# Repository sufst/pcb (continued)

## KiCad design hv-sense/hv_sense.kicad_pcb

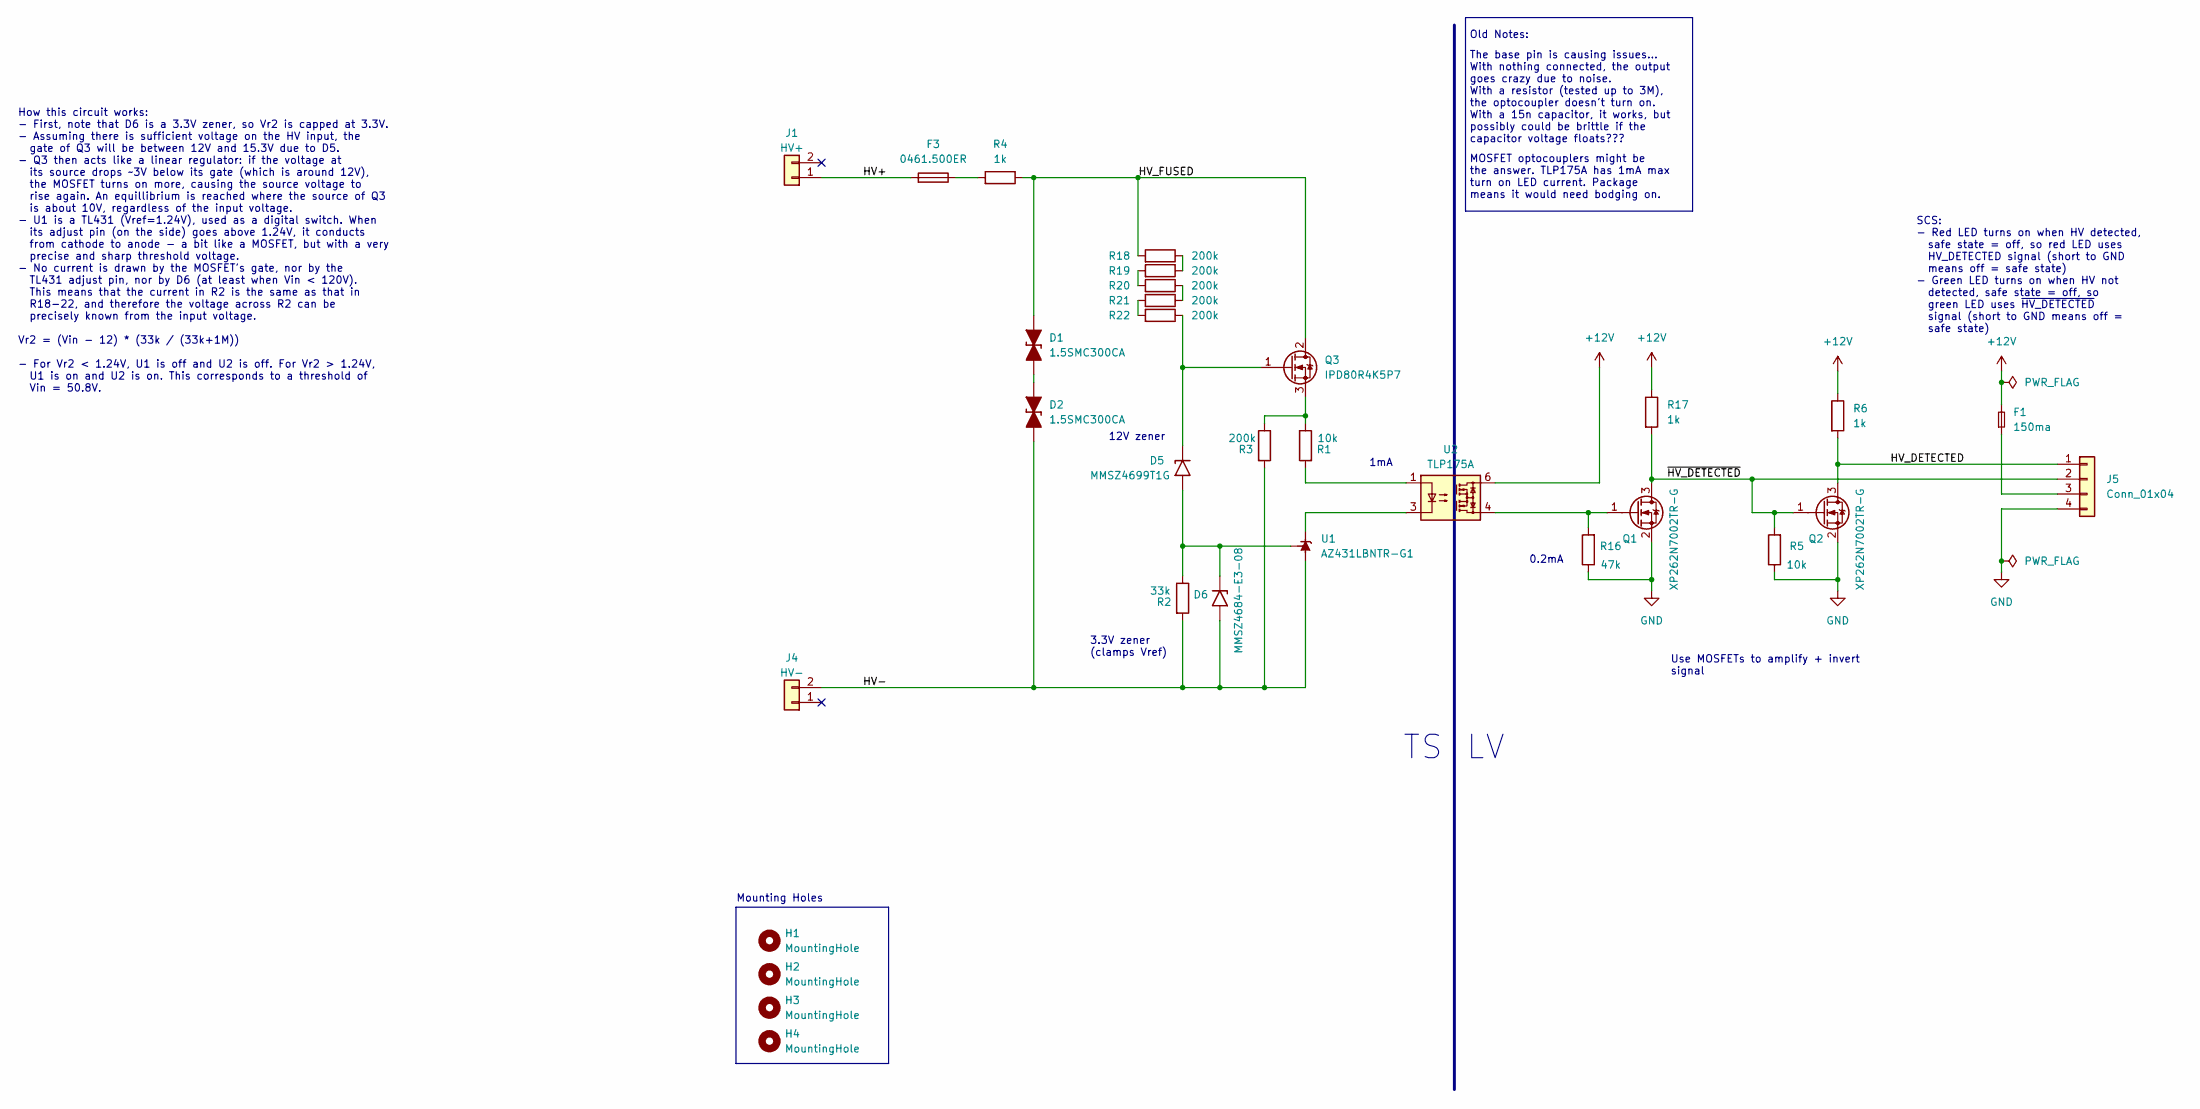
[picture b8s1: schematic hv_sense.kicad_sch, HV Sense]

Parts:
D1, D2: 1.5SMC300CA; D_SMC_TVS
D5: MMSZ4699T1G; D_SOD-123
D6: MMSZ4684-E3-08; D_SOD-123
F1: 150ma; Fuse_0805_2012Metric
F3: 0461.500ER; Littelfuse-04611-25ER
H1, H2, H3, H4: MountingHole; MountingHole_4.3mm_M4
J1: HV+; Molex_Micro-Fit_3.0_43045-0212_2x01_P3.00mm_Vertical
J4: HV-; Molex_Micro-Fit_3.0_43045-0212_2x01_P3.00mm_Vertical
J5: Conn_01x04; Molex_Micro-Fit_3.0_43045-0412_2x02_P3.00mm_Vertical
Q1, Q2: XP262N7002TR-G; SOT-23
Q3: IPD80R4K5P7; TO-252-2
R1, R5: 10k; R_0805_2012Metric_Pad1.20x1.40mm_HandSolder
R2: 33k; R_0805_2012Metric_Pad1.20x1.40mm_HandSolder
R3, R18, R19, R20, R21, R22: 200k; R_0805_2012Metric_Pad1.20x1.40mm_HandSolder
R4: 1k; R_2512_6332Metric
R6, R17: 1k; R_0805_2012Metric_Pad1.20x1.40mm_HandSolder
R16: 47k; R_0805_2012Metric_Pad1.20x1.40mm_HandSolder
U1: AZ431LBNTR-G1; SOT-23_Handsoldering
U2: TLP175A; MFSOP6-4_4.4x3.6mm_P1.27mm

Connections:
+12V: F1.2, R6.1, R17.1, U2.6
/HV+: F3.2, J1.1
/HV-: D2.1 (K), D6.2 (A2), J4.2, R2.2, R3.2, U1.3 (A)
/HV_DETECTED: J5.1, Q2.3 (D), R6.2
/HV_FUSED: D1.2 (A), Q3.2 (D), R4.1, R18.2
/~HV_DETECTED: J5.2, Q1.3 (D), Q2.1 (G), R5.2, R17.2
GND: J5.4, Q1.2 (S), Q2.2 (S), R5.1, R16.1
unnamed: D1.1 (K), D2.2 (A)
unnamed: D5.1 (A1), Q3.1 (G), R22.1
unnamed: D5.2 (A2), D6.1 (A1), R2.1, U1.1 (REF)
unnamed: F3.1, R4.2
unnamed: F1.1, J5.3
unnamed: Q1.1 (G), R16.2, U2.4
unnamed: Q3.3 (S), R1.1, R3.1
unnamed: R1.2, U2.1
unnamed: R18.1, R19.1
unnamed: R19.2, R20.2
unnamed: R20.1, R21.1
unnamed: R21.2, R22.2
unnamed: U1.2 (K), U2.3

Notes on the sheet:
0.2mA
SCS: - Red LED turns on when HV detected, safe state = off, so red LED uses HV_DETECTED signal (short to GND means off = safe state) - Green LED turns on when HV not detected, safe state = off, so green LED uses ~{HV_DETECTED} signal (short to GND means off = safe state)
Mounting Holes
12V zener
Use MOSFETs to amplify + invert signal
How this circuit works: - First, note that D6 is a 3.3V zener, so Vr2 is capped at 3.3V. - Assuming there is sufficient voltage on the HV input, the gate of Q3 will be between 12V and 15.3V due to D5. - Q3 then acts like a linear regulator: if the voltage at its source drops ~3V below its gate (whi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
3.3V zener (clamps Vref)
Old Notes:
The base pin is causing issues... With nothing connected, the output goes crazy due to noise. With a resistor (tested up to 3M), the optocoupler doesn't turn on. With a 15n capacitor, it works, but possibly could be brittle if the capacitor voltage floats???
1mA
MOSFET optocouplers might be the answer. TLP175A has 1mA max turn on LED current. Package means it would need bodging on.

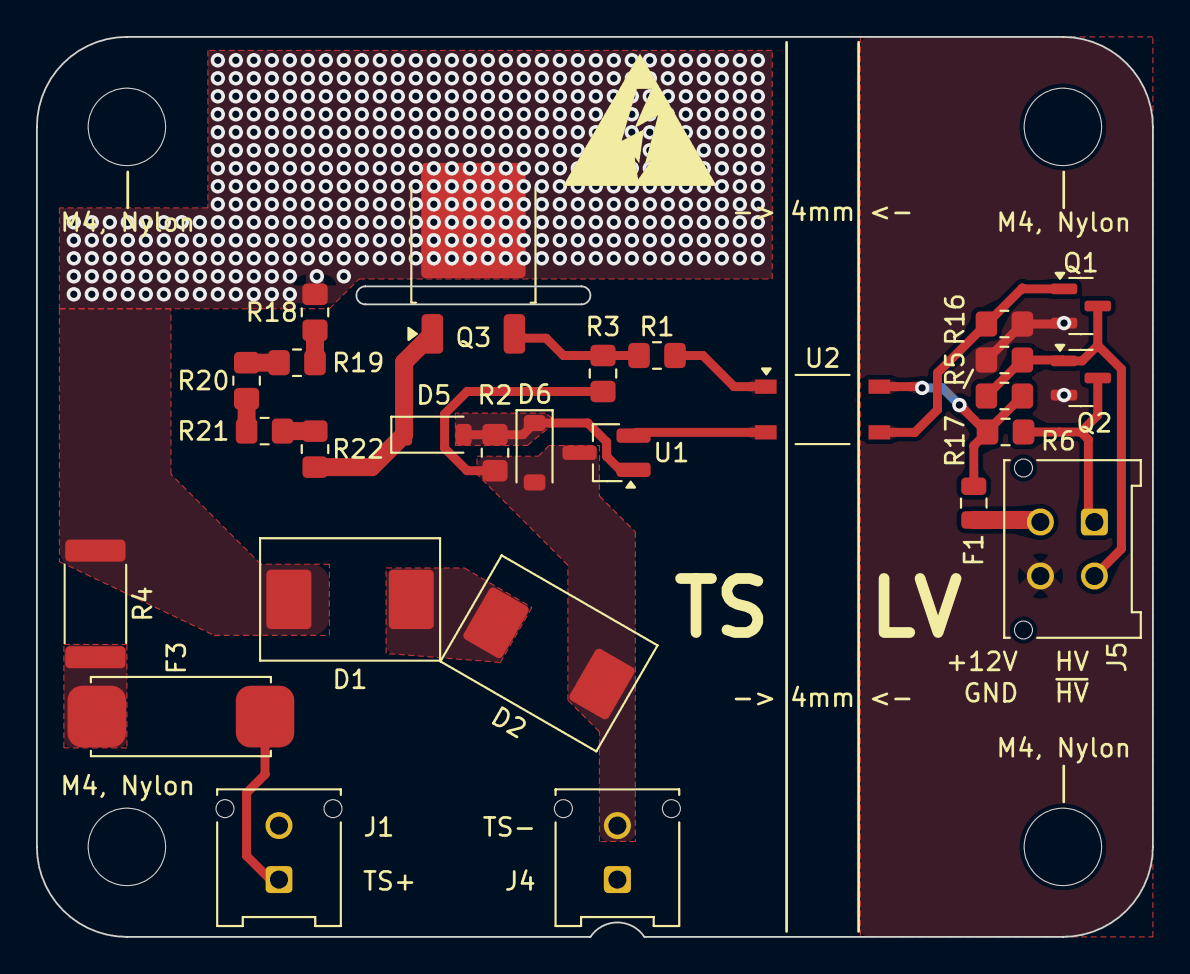
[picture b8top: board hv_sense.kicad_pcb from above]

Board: 2 copper layers, 62.0 x 50.0 mm, 31 parts (0 on the bottom side), 20 nets.

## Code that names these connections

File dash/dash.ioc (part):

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Mcu.Name=STM32F746ZGTx
Mcu.Package=LQFP144
Mcu.UserName=STM32F746ZGTx
PA0/WKUP.GPIOParameters=GPIO_Label
PA0/WKUP.GPIO_Label=BACKLIGHT_PWM
PA0/WKUP.Signal=S_TIM2_CH1_ETR
PA1.Mode=RGB666
PA1.Signal=LTDC_R2
PA11.Mode=CAN_Activate
PA11.Signal=CAN1_RX
PA12.Mode=CAN_Activate
PA12.Signal=CAN1_TX
PA15.GPIOParameters=GPIO_Label
PA15.GPIO_Label=SD_CARD_DETECT
PA15.Signal=GPIO_Output
PA3.Mode=RGB666
PA3.Signal=LTDC_B5
PA4.Mode=RGB666
PA4.Signal=LTDC_VSYNC
PA5.Mode=RGB666
PA5.Signal=LTDC_R4
PA6.Mode=RGB666
PA6.Signal=LTDC_G2
PA7.Signal=FMC_SDNWE
PB0.Mode=RGB666
PB0.Signal=LTDC_R3
PB1.Mode=RGB666
PB1.Signal=LTDC_R6
PB10.Mode=RGB666
PB10.Signal=LTDC_G4
PB11.Mode=RGB666
PB11.Signal=LTDC_G5
PB12.GPIOParameters=GPIO_Label
PB12.GPIO_Label=SPI2_CS
PB12.Signal=GPIO_Output
PB13.Mode=Full_Duplex_Master
PB13.Signal=SPI2_SCK
PB14.Mode=Full_Duplex_Master
PB14.Signal=SPI2_MISO
PB15.Mode=Full_Duplex_Master
PB15.Signal=SPI2_MOSI
PB5.Mode=CAN_Activate
PB5.Signal=CAN2_RX
PB6.Mode=CAN_Activate
PB6.Signal=CAN2_TX
PB8.Mode=RGB666
PB8.Signal=LTDC_B6
PB9.Mode=RGB666
PB9.Signal=LTDC_B7
PC0.Mode=RGB666
PC0.Signal=LTDC_R5
PC10.Mode=SD_4_bits_Wide_bus
PC10.Signal=SDMMC1_D2
PC11.Mode=SD_4_bits_Wide_bus
PC11.Signal=SDMMC1_D3
PC12.Mode=SD_4_bits_Wide_bus
PC12.Signal=SDMMC1_CK
PC2.Mode=SdramChipSelect1_1
PC2.Signal=FMC_SDNE0
PC3.Mode=SdramChipSelect1_1
PC3.Signal=FMC_SDCKE0
PC5.GPIOParameters=GPIO_Label
PC5.GPIO_Label=LCD_DISP
PC5.Signal=GPIO_Output
PC6.Mode=RGB666
PC6.Signal=LTDC_HSYNC
PC7.Mode=RGB666
PC7.Signal=LTDC_G6
PC8.Mode=SD_4_bits_Wide_bus
PC8.Signal=SDMMC1_D0
PC9.Mode=SD_4_bits_Wide_bus
PC9.Signal=SDMMC1_D1
PD0.Signal=FMC_D2_DA2
PD1.Signal=FMC_D3_DA3
PD10.Signal=FMC_D15_DA15
PD11.GPIOParameters=GPIO_Label
PD11.GPIO_Label=TOUCH_IRQ
PD11.Signal=GPXTI11
PD12.GPIOParameters=GPIO_Label
PD12.GPIO_Label=TOUCH_BUSY
PD12.Signal=GPIO_Input
PD14.Signal=FMC_D0_DA0
PD15.Signal=FMC_D1_DA1
PD2.Mode=SD_4_bits_Wide_bus
PD2.Signal=SDMMC1_CMD
PD3.Mode=RGB666
PD3.Signal=LTDC_G7
PD6.Mode=RGB666
PD6.Signal=LTDC_B2
PD8.Signal=FMC_D13_DA13
PD9.Signal=FMC_D14_DA14
PE0.Signal=FMC_NBL0
PE1.Signal=FMC_NBL1
PE10.Signal=FMC_D7_DA7
PE11.Signal=FMC_D8_DA8
PE12.Signal=FMC_D9_DA9
PE13.Signal=FMC_D10_DA10
PE14.Signal=FMC_D11_DA11
PE15.Signal=FMC_D12_DA12
PE7.Signal=FMC_D4_DA4
PE8.Signal=FMC_D5_DA5
PE9.Signal=FMC_D6_DA6
PF0.Signal=FMC_A0
PF1.Signal=FMC_A1
PF10.Mode=RGB666
PF10.Signal=LTDC_DE
PF11.Signal=FMC_SDNRAS
PF12.Signal=FMC_A6
PF13.Signal=FMC_A7
PF14.Signal=FMC_A8
PF15.Signal=FMC_A9
PF2.Signal=FMC_A2
PF3.Signal=FMC_A3
PF4.Signal=FMC_A4
PF5.Signal=FMC_A5
PG0.Signal=FMC_A10
PG1.Signal=FMC_A11
PG10.Mode=RGB666
PG10.Signal=LTDC_G3
PG11.Mode=RGB666
PG11.Signal=LTDC_B3
PG12.Mode=RGB666
PG12.Signal=LTDC_B4
PG15.Signal=FMC_SDNCAS
PG4.Signal=FMC_A14_BA0
PG5.Signal=FMC_A15_BA1
PG6.Mode=RGB666
PG6.Signal=LTDC_R7
PG7.Mode=RGB666
PG7.Signal=LTDC_CLK
PG8.Signal=FMC_SDCLK
RCC.HSE_VALUE=25000000
board=custom

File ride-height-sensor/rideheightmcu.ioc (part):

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Mcu.Name=STM32C092FBPx
Mcu.Package=TSSOP20
Mcu.UserName=STM32C092FBPx
PA0.GPIOParameters=GPIO_Label
PA0.GPIO_Label=PPS_IN
PA0.Signal=S_TIM1_CH1
PA1.GPIOParameters=GPIO_Label
PA1.GPIO_Label=JPR1
PA1.Signal=GPIO_Input
PA11\ [PA9].Mode=FDCAN_Activate
PA11\ [PA9].Signal=FDCAN1_RX
PA12\ [PA10].Mode=FDCAN_Activate
PA12\ [PA10].Signal=FDCAN1_TX
PA13.Mode=Serial_Wire
PA13.Signal=DEBUG_SWDIO
PA14-BOOT0.Mode=Serial_Wire
PA14-BOOT0.Signal=DEBUG_SWCLK
PA14-BOOT0__PA15.StandardMode=true
PA2.GPIOParameters=GPIO_Label
PA2.GPIO_Label=JPR2
PA2.Signal=GPIO_Input
PA3.GPIOParameters=GPIO_Label
PA3.GPIO_Label=XSHUT
PA3.Signal=GPIO_Output
PA4.GPIOParameters=GPIO_Label
PA4.GPIO_Label=BTN
PA4.Signal=GPIO_Input
PA5.GPIOParameters=GPIO_Label
PA5.GPIO_Label=LED_ACTIVITY
PA5.Signal=GPIO_Output
PA6.GPIOParameters=GPIO_Label
PA6.GPIO_Label=LED_CAN_ACTIVITY
PA6.Signal=GPIO_Output
PA7.GPIOParameters=GPIO_Label
PA7.GPIO_Label=LED_HEARTBEAT
PA7.Signal=GPIO_Output
PB0.GPIOParameters=GPIO_Label
PB0.GPIO_Label=interrupt pin
PB0.Signal=GPXTI0
PB0__PB1__PB2__PA8.StandardMode=true
PB3__PB4__PB5__PB6.StandardMode=true
PB6.Mode=I2C
PB6.Signal=I2C1_SCL
PB7.Mode=I2C
PB7.Signal=I2C1_SDA
PB7__PB8.StandardMode=true
PC14-OSCX_IN(PC14).Mode=HSE-External-Oscillator
PC14-OSCX_IN(PC14).Signal=RCC_OSCX_IN
PC15-OSCX_OUT(PC15).Mode=HSE-External-Oscillator
PC15-OSCX_OUT(PC15).Signal=RCC_OSCX_OUT
RCC.HSE_VALUE=25000000
RCC.SYSCLKFreq_VALUE=25000000
RCC.SYSCLKSource=RCC_SYSCLKSOURCE_HSE
board=custom

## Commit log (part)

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2026-02-04 Reviewing with anna
2026-02-05 Added buck-boost schematic
2026-02-05 Via farms are a lie made by big drill to sell more drill bits
2026-02-05 Adding 3d models, changing resistors
2026-02-05 Reviewing and changing
2026-02-05 Add warning
2026-02-06 Added flat clamp instead of unidirectional tvs
2026-02-07 Updated BOM, ready for review
2026-02-07 move silkscreen
2026-02-07 Generated pdf
2026-02-07 Partially complete BOM
    under Mouser project "New VCU"
2026-02-07 Add clamped_div schematic and update symbols/libs
    Add a new clamped_div.kicad_sch implementing a voltage divider/clamped input (optional zener diodes, resistor network and notes). Update therm.kicad_sch to include a project title block and add an ES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
2026-02-07 BOM Complete
2026-02-09 Updated BOM
2026-02-10 archive sensor board
2026-02-10 rename thermistor board to can-node
2026-02-10 finish can-node schematic, some libraries are missing
2026-02-10 Done mostly all of design for schematic
    Hello everybody my name is markiplier,
    need to add connectors to schematic
    **IGNORE GPS PCB IT IS OUTDATED**
2026-02-10 Schematic done i think
    Peetah The Horse Is Here
2026-02-10 switch B.Cu and In1.Cu routing, update silkscreen and other fixes
2026-02-12 Added 26 pin harwin connector
2026-02-12 Update TLV9101IDBVR
2026-02-12 Added buffered input
    Also footprint assignments messed up rip
2026-02-12 forgot to save
2026-02-13 Implemented APPS SCS biasing
    TODO: fusing buck-boost regulated output?
2026-02-17 Made the file
2026-02-17 help
2026-02-17 traces to 0.5 and footprint to 0805 done
2026-02-17 pcbdesign
2026-02-17 made it a lill bit neater
    not much
2026-02-17 added the logo and version
    still need to add the pin, button descriptions and basic labels
2026-02-17 gOTrIDoFtHEcAMELS
2026-02-17 Added outline of pcb
2026-02-18 reroute can-node
2026-02-18 fix some silkscreen issues + add more vias
2026-02-18 try and fix issue with git
2026-02-19 SILKSCREEN DONNEEE!!!
2026-02-19 routing fixes
2026-02-20 Changes
    Production on pause
2026-02-21 production files
2026-02-21 Update to only have CAN, move BMS taps to loom
2026-02-24 Added necessary STM things to schematic
2026-02-24 Footprint for mating card made
2026-02-24 Added camera and layout things
2026-02-25 Oopsie relocated mating card footprint to vcu-debug-card from vcu
2026-02-25 Pinned SUFST library why is github being weird :(
2026-02-25 Added some leds :)
2026-02-26 Attempted to fix merge error
2026-03-01 Switched back to molex
2026-03-01 saved schematic
2026-03-02 Added Apps sensor
2026-03-03 Added mating card footprint to symbol
2026-03-03 addeed I2C sevensegs
2026-03-03 Added footprint for seven segment display
2026-03-03 Changed name of seven segment and added link to datasheet
2026-03-03 Footprint :(
2026-03-03 added dip BOOYAH
2026-03-05 uhhh
2026-03-08 connected dip
2026-03-09 Updated mating card footprint
    Added the gap for pins 15 and 16 and the part at the bottom
2026-03-10 added values
2026-03-10 changed shape of pcb a bit to allow room for the mating card
2026-03-10 added led footprints
2026-03-10 added db9 connector symbols
2026-03-10 FinalFinalFinalActuallyReallyThisTimeV3
2026-03-10 being more aesthetic ofc
2026-03-10 editing labels
2026-03-10 stole from old card for old pcb
    kidnapped some headers we may be able to use not sure yet
2026-03-10 Revert "Added RTC :)"
    This reverts commit d669b6d96096c189c741b15f89f04d634790e15c.
2026-03-10 more labelling YIPPEEEEE
2026-03-10 Stuff (footprint improved and added to pcb yay)
    I make it shake that ass
2026-03-10 didnt do much was feeling fabuloussssssssssssssss
2026-03-12 fix molex connector pin mappings/routing and edge layout
2026-03-12 improve crystal layout
2026-03-12 Added 3d models
2026-03-14 Completed SDC Loop
2026-03-14 Fixed reverse prot mosfet pinout
2026-03-14 few corrections for a rev2
2026-03-15 create project
2026-03-16 Schematic
2026-03-16 Add IMD
2026-03-17 Added kicad_pro
    theres a project now
2026-03-17 changed label
2026-03-17 Placed RTC
    did so much wow
2026-03-17 Added symbol and footprint for TPS4813-Q1
2026-03-17 Moved the Project
2026-03-17 added some pinouts whoopee
    hell yeah so awesome
2026-03-17 one singular label wow
2026-03-19 esf lies
2026-03-19 Created dev-board for TPS48130-Q1
2026-03-19 Revised R1 footprint
2026-03-19 Lv bms highside (#152)
    * Created dev-board for TPS48130-Q1
    * Revised R1 footprint
    * v1.0.0 release
    ---------
2026-03-20 new step
2026-03-20 Change file structure for molex version
2026-03-20 Rename project files
2026-03-20 Updated values for ldo
2026-03-20 Route CAN
2026-03-21 added LDO and other routing things
2026-03-21 Added IMU + Temp
2026-03-21 Please unbreak the schematic
2026-03-21 Please unbreak the schematic again
    2nd times the charm
2026-03-21 JUST ONE MORE COMMIT
2026-03-21 I can't see what I'm committing
2026-03-21 please don't implode
2026-03-21 file can open, needs reconstruction
2026-03-21 DRC fears me
2026-03-21 layout
2026-03-21 playing around with layout
2026-03-21 cut down PCB for accu
2026-03-21 Redo File structure for differennt number of channel boards
2026-03-21 v1.2.0 Release
2026-03-21 Updated for SCS compliance
2026-03-21 generate fab stuff
2026-03-21 pcb basically done, needs a bit of silkscreen
2026-03-21 Fixed board outline
2026-03-21 Add cuts and silkscreen?
    Just a concept
2026-03-22 Add teardrops
2026-03-22 Fix silkscreen labels, and generate new production files
2026-03-22 fix issue of resistor on wrong net
2026-03-22 1.0.0 Release
2026-03-22 Re-release v1.0.0 16Ch and 8Ch sensor hub
2026-03-22 Generate production files
2026-03-23 Altium Capture for future use and ESF schematic
2026-03-23 Altium import
    pls don't explode
2026-03-23 v1.0.0 prerelease
2026-03-23 Added fusing schematics
2026-03-23 Added BSPD sheet
2026-03-24 Finished shutdown circuit
2026-03-24 started schematic for tsac
2026-03-24 maybe BSPD done?
2026-03-24 Updated SDC and started TSAL
2026-03-24 Fixed merge conflicts
2026-03-24 updated BSPD schematic
2026-03-24 TSAL Red light updates
2026-03-24 Finished TSAL Red and started TSAL green
2026-03-25 Work on latching
2026-03-25 Created LVMS footprint, added fuse holder
2026-03-25 i forgor
2026-03-25 Create new latching sheets
2026-03-25 Finished latching AMS and IMD
2026-03-25 corrected BSPD schematic
2026-03-25 Finish TSAL LED
2026-03-25 Tsal Green stuff
2026-03-25 Tsal stuff
2026-03-25 nearly done ts schematics
2026-03-26 ts fusing schematic for checking
2026-03-26 finish tsal
2026-03-26 fusing
2026-03-26 fusing done
2026-03-27 tsal final final final no take backs
2026-03-27 changed a few lables on fusing docs
2026-03-27 Updated Fusing PDFs
2026-03-27 v1.2.0
2026-03-28 Fix dodgy shit
2026-03-28 Fixed STEP and silkscreen
2026-03-28 Updated library
2026-03-28 Generate production files and rename project
2026-03-28 Release Segment Switch v1.0.0 (#155)
    * v1.0.0 prerelease
    * v1.0.0 Release
    * Fix dodgy shit
    * Fixed STEP and silkscreen
    * Generate production files and rename project
    ---------
2026-03-28 v1.2.0 Release
    Just one more PCB
2026-03-28 Fixed ERC errors
2026-03-28 Release Right Sidepanel v1.2.0 (#156)
    * Created LVMS footprint, added fuse holder
    * v1.0.0 prerelease
    just one more PCB...
    * v1.1.0
    Added blade fuse springs, LED indicators for fuses
    * v1.2.0
2026-03-28 fix dash ldo name
2026-03-29 Started proper layout
2026-03-30 More layout things
2026-03-30 Generated iBOM
2026-03-30 More routing
2026-04-01 Clear all DRC errors and warnings
2026-04-01 a couple of tweaks
2026-04-01 more tweaks
2026-04-01 updated iBOM
2026-04-01 tweaks
2026-04-01 Added temp sensor and tvs diode for rs232
2026-04-01 Added testpoints
2026-04-02 rerouted some things and added SPI
2026-04-03 Added IMU and Magnetometer
2026-04-03 adjust some things
2026-04-03 Added pps tvs
2026-04-04 things idk
2026-04-04 updated LDO, added tvs stuff
2026-04-04 Rename project
2026-04-04 Solve DRC errors
2026-04-04 Fix ERC errors
2026-04-04 Generate fabrication outputs
2026-04-04 Forgot to do teardrops. Regenerated production files
2026-04-04 Release v1.0.0
2026-04-04 Revert <trc.kicad_pro> to commit <52a5c51>
2026-04-05 stole some bits and bobs
    IDK what im doing so i took voltage regulator and CAN bus interface sub systems from the CAN repeater PCB schematic
    probaly shouldnt do that but idk
    also i couldnt find a good schematic for the micro controller so i idid my own one thats why its so shit
2026-04-05 changed it
    swaped the wrong thing for the right thing
2026-04-05 im lost
    i think its better
    or its much much worse
2026-04-06 generate step for can-repeater-H
2026-04-09 symultaniously more and less fucked
    did more footprints
    started PCB
    sufst library not working
    used wrong connector [fixme]
    its a mess
2026-04-10 converted to kicad 9
    pcb is gone
    :(
2026-04-21 Putting them libraries for da-wei
2026-04-21 messing w the layout
2026-04-21 JTAG connected
    epic importgant stuff
2026-04-21 test point acquired
2026-04-21 RTC updated
2026-04-21 RTC again :(
2026-04-21 yoyoyo usart
2026-04-27 mcupinout
2026-04-28 new mcu pinout
2026-04-28 resuhffling
2026-04-28 Changed dip switch info
2026-04-28 Moved RTC slightly and solved problem
2026-04-28 added load capacitors
2026-04-28 Fixes?
2026-04-29 more compact tm
2026-04-29 initial push
2026-05-01 general update
2026-05-02 BOOM different RTC
2026-05-02 small annotation chanbes
2026-05-04 small errors fix
2026-05-04 Schem finished probably
2026-05-04 Updated silk and tweaked fills
    Ready for v1.1 release
2026-05-04 i THINK i recovered the conflict, added silk and vias
2026-05-04 refixed fills
2026-05-05 Crystal footprint/datasheet
2026-05-05 Revert "Merge branch 'vcu-debug-card' of https://github.com/sufst/pcb into vcu-debug-card"
    This reverts commit 19c90c9e1964f9a77721238ffb053e71d11ffb83, reversing
    changes made to d848e882c473c7032f10bd9c1ce48d7e836cb1cd.
2026-05-05 Reapply "Merge branch 'vcu-debug-card' of https://github.com/sufst/pcb into vcu-debug-card"
    This reverts commit 6bca00b58b8072da05f5c3ad163965dccf6e5c8f.
2026-05-05 Stuff happened fr
2026-05-05 Datasheet
2026-05-05 odsohflsiadhflashdfilh
2026-05-05 Stuff
2026-05-05 Revert "Stuff"
    This reverts commit 3a6473118316d1d70345c749b9a40d21425ae492.
2026-05-05 Revert "Datasheet"
    This reverts commit 21f37d1297ec6f23ad6434b0e9a6d112324a7257.
2026-05-05 ahhh
2026-05-11 rename can-node to sensor-hub, make the two variants share components as shared schematic files, improve silkscreen labels, use GLV_PROT to power op-amp buffers instead of +3V3 and add bridge to bypa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
2026-05-11 don't update sufst-lib
2026-05-11 update batak board (#159)
    * update batak board
    * don't update sufst-lib
2026-05-12 Tweak layout around connectors
2026-05-12 connect dipswitch + crystal footprint
2026-05-12 Changed stuff about DE9 pins
2026-05-12 decoupling capacitor footprint etc
2026-05-12 add de9 footprints etc
2026-05-12 almost done w footprints
2026-05-12 battery holder footprint
2026-05-12 removed old uart
2026-05-12 Fixed errors in pcb editor
2026-05-12 more changed
2026-05-12 pbc loaded yay
2026-05-12 Fixed Da-Weis stuff
2026-05-12 pcb editor
2026-05-12 Made GLV Smaller and Fix C2
2026-05-12 Pcb editing MORE NEVER ENOUGH EDITING
2026-05-12 layout (without routing)
2026-05-16 Added Highside Switch. Removed relay and related circuitry. Combined the two ON & OFF buttons into a single ON/OFF toggle.
    Changes:
    - Removed relay and related circuitry
    - Added HS switch
    - Added indicator lights to signal which gates are open
    - Replaced the separate on and off buttons with a single on/off button and connected it to J3
    - Renamed various "5v" silkscreen labels to "3.3v"
2026-05-20 purchase pcb
2026-06-09 change resistors
2026-06-12 rename can-node to sensor-hub and delete old sensor-board artifacts
2026-06-12 Sensor Hub 1.2.0 Release (#154)
    * progress from last week
    * temp update
    To find GND issue
    * Current Design 18/11/25
    Current agreed design at the time of EOS, by Adam and Ray contributions
    * Update library paths and clean up PCB net segments
2026-06-13 added BOM PN and cost
2026-06-14 correct TSMS naming on RSP pcb
2026-06-15 Add 3d models
2026-06-20 fix apps sensor bias on wrong pin
